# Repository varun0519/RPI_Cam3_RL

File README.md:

# RPI_Cam3_RL

## 🚀 How to Use Automation Script to generate fabrication outputs

### 🔧 Command Line (Terminal)

Run the following command **from the project directory** (where `.kicad_pro` file is located):

```bash
make
```
To generate zip of Gerbers for fabrication:
```bash
make release
```

Or run the script directly with Python:
```bash
python3 scripts/export_fab_outputs.py
```

### 3D view
#### Top View

#### Bottom View

#### Perspective View

### Schematic
[RPI_Cam3_RL_schematic.pdf](output/RPI_Cam3_RL_schematic.pdf)

### BOM
[RPI_Cam3_RL_BOM.xlsx](output/RPI_Cam3_RL_BOM.xlsx)

### Top Assembly
[RPI_Cam3_RL_Top_Assembly.pdf](output/RPI_Cam3_RL_Top_Assembly.pdf)

### Bottom Assembly
[RPI_Cam3_RL_Bottom_Assembly.pdf](output/RPI_Cam3_RL_Bottom_Assembly.pdf)

### Interactive BOM
Download and open [ibom.html](bom/ibom.html) in browser

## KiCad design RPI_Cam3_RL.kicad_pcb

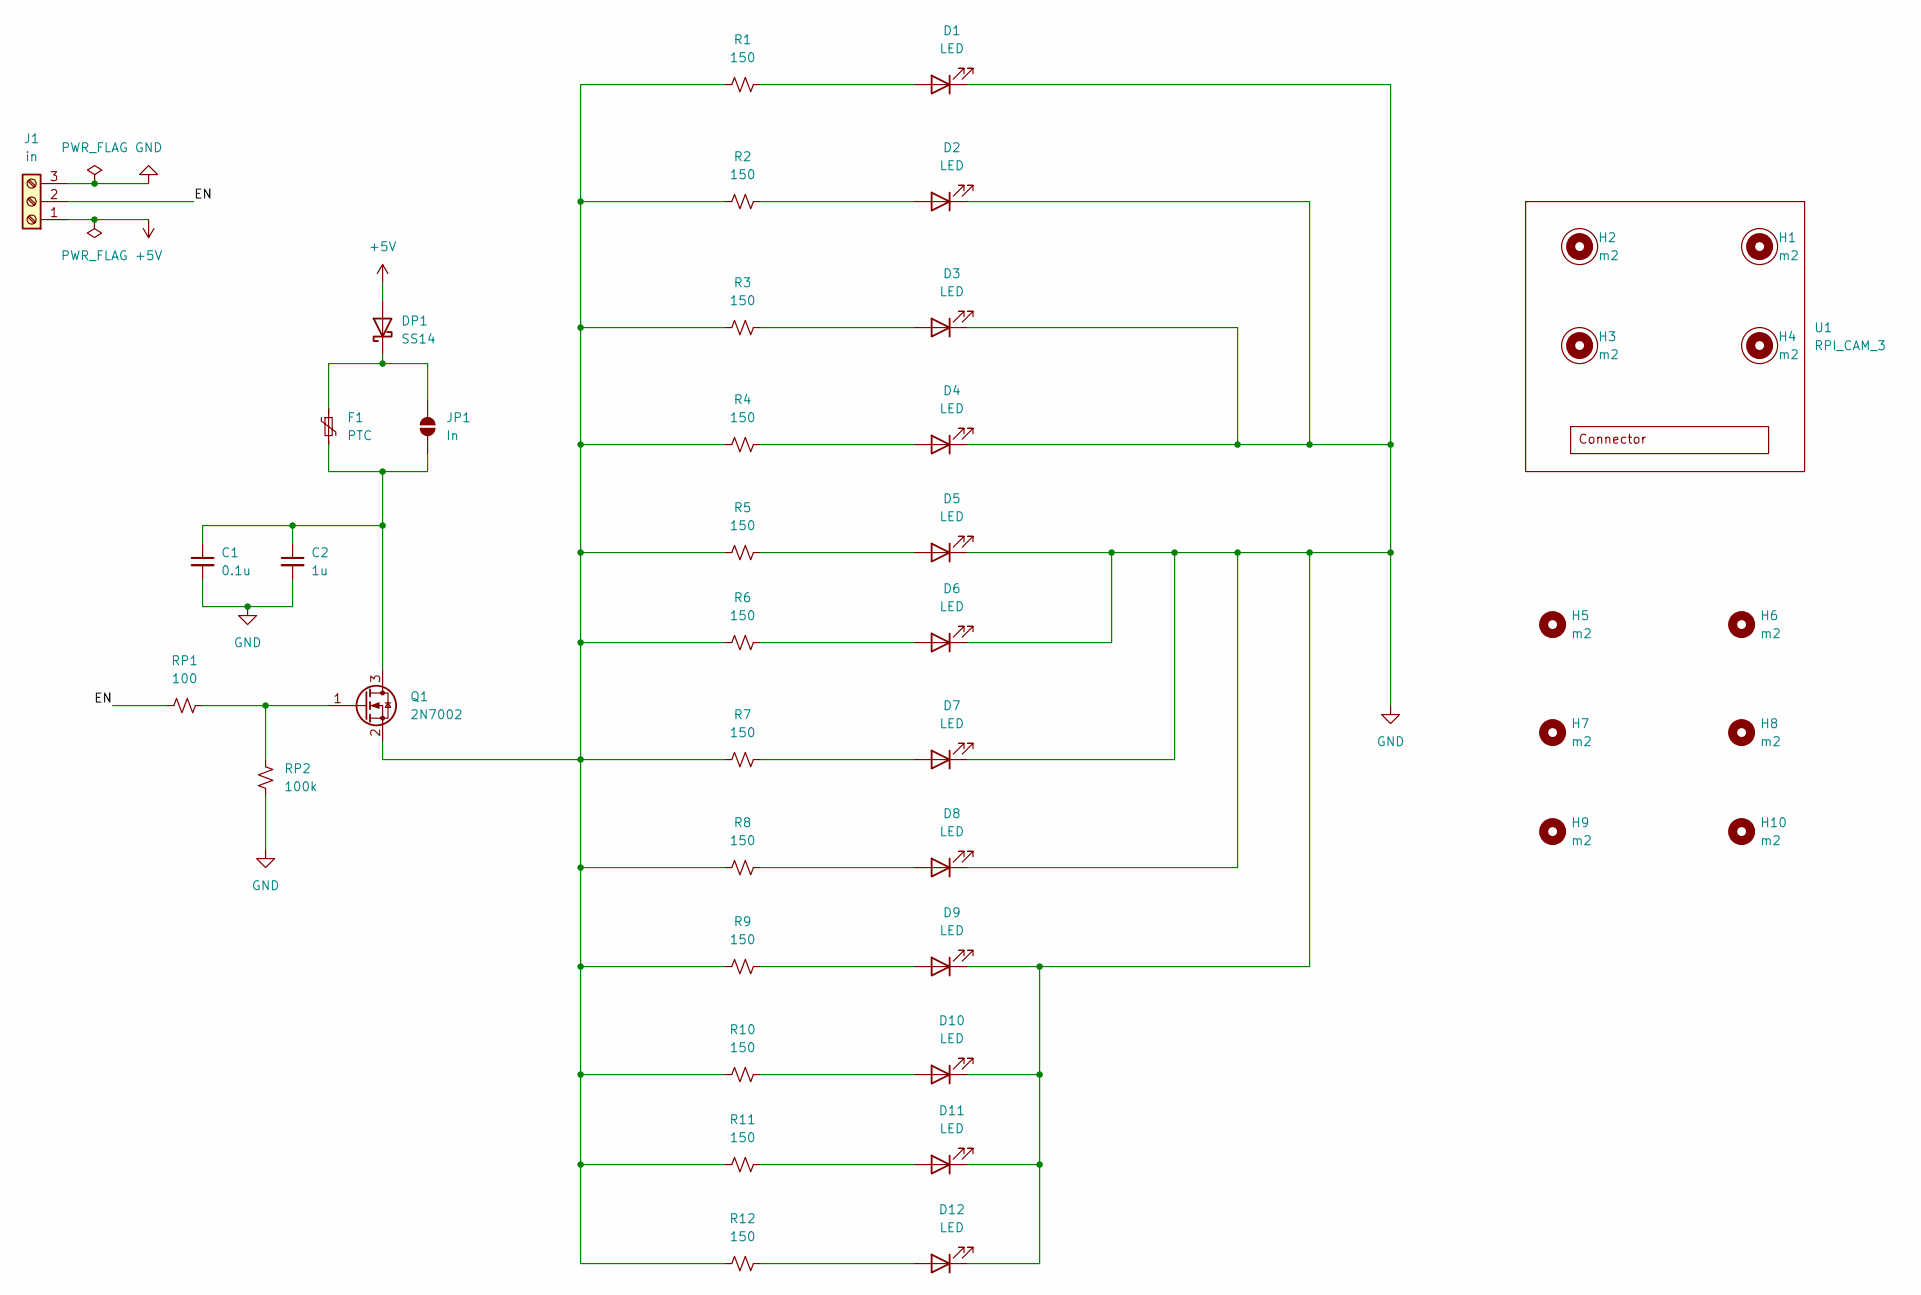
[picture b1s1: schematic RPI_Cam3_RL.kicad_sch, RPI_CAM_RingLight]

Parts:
C1: 0.1u; C_0805_2012Metric_Pad1.18x1.45mm_HandSolder
C2: 1u; C_0805_2012Metric_Pad1.18x1.45mm_HandSolder
D1, D2, D3, D4, D5, D6, D7, D8, D9, D10, D11, D12: LED; LED_PLCC_2835_Handsoldering
DP1: SS14; D_SMA
F1: PTC; R_0805_2012Metric_Pad1.20x1.40mm_HandSolder
H1, H2, H3, H4: m2; MountingHole_2.2mm_M2
H5, H6, H7, H8, H9, H10: m2; MountingHole_3.2mm_M3
J1: in; JST_EH_S3B-EH_1x03_P2.50mm_Horizontal
JP1: In; SolderJumper-2_P1.3mm_Open_RoundedPad1.0x1.5mm
Q1: 2N7002; SOT-23_Handsoldering
R1, R2, R3, R4, R5, R6, R7, R8, R9, R10, R11, R12: 150; R_0805_2012Metric_Pad1.20x1.40mm_HandSolder
RP1: 100; R_0805_2012Metric_Pad1.20x1.40mm_HandSolder
RP2: 100k; R_0805_2012Metric_Pad1.20x1.40mm_HandSolder
U1: RPI_CAM_3; RPI_Cam3

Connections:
+5V: DP1.2 (A), J1.1
/EN: J1.2, RP1.1
GND: C1.2, C2.2, D1.1 (K), D2.1 (K), D3.1 (K), D4.1 (K), D5.1 (K), D6.1 (K), D7.1 (K), D8.1 (K), D9.1 (K), D10.1 (K), D11.1 (K), D12.1 (K), J1.3, RP2.1
unnamed: D1.2 (A), R1.2
unnamed: D2.2 (A), R2.2
unnamed: D3.2 (A), R3.2
unnamed: D4.2 (A), R4.2
unnamed: D5.2 (A), R5.2
unnamed: D6.2 (A), R6.2
unnamed: D7.2 (A), R7.2
unnamed: D8.2 (A), R8.2
unnamed: D9.2 (A), R9.2
unnamed: D10.2 (A), R10.2
unnamed: D11.2 (A), R11.2
unnamed: D12.2 (A), R12.2
unnamed: DP1.1 (K), F1.1, JP1.2 (B)
unnamed: C1.1, C2.1, F1.2, JP1.1 (A), Q1.3 (D)
unnamed: Q1.1 (G), RP1.2, RP2.2
unnamed: Q1.2 (S), R1.1, R2.1, R3.1, R4.1, R5.1, R6.1, R7.1, R8.1, R9.1, R10.1, R11.1, R12.1

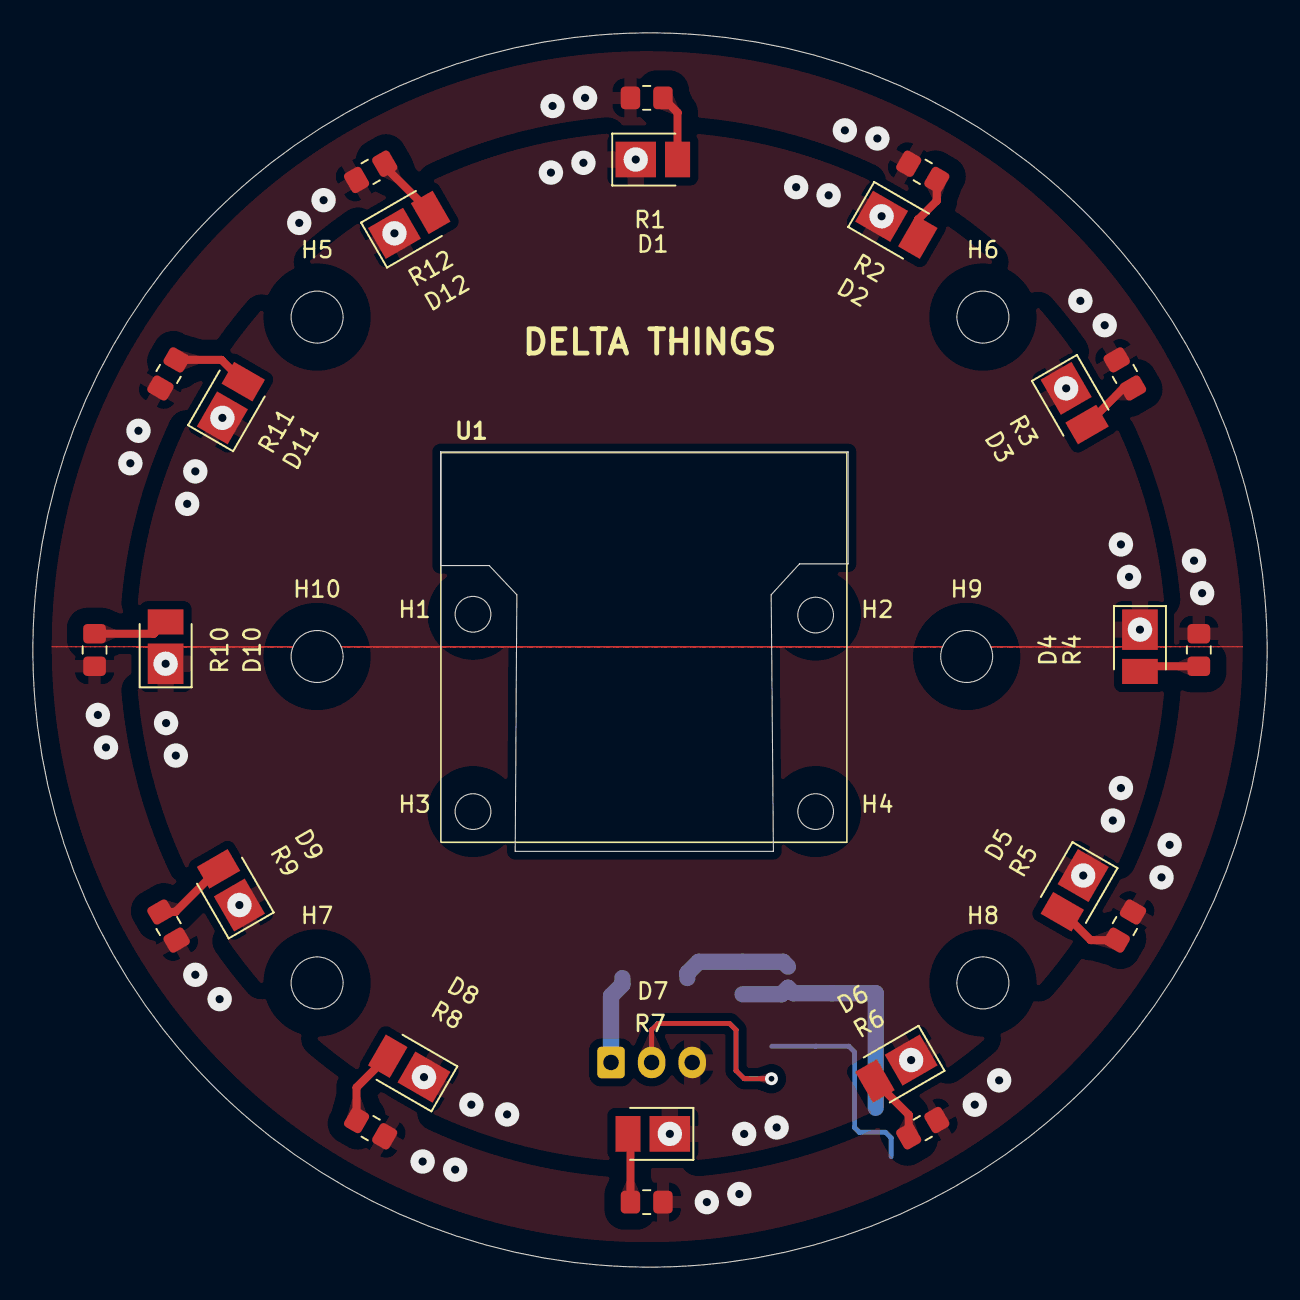
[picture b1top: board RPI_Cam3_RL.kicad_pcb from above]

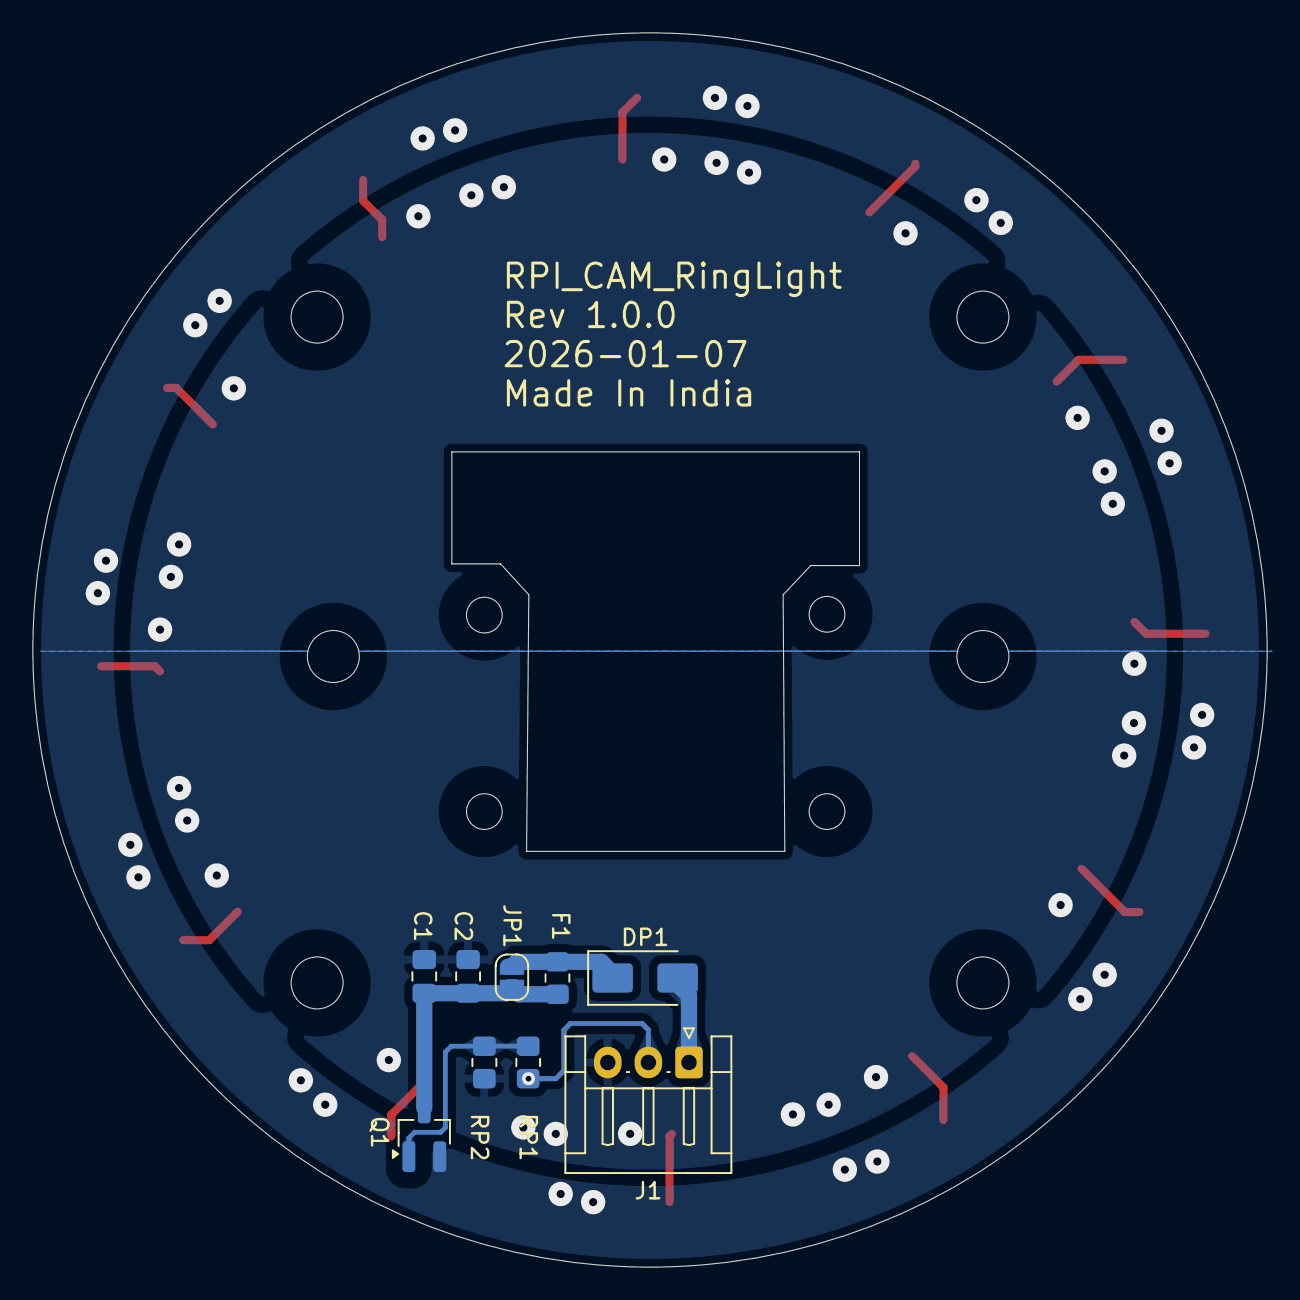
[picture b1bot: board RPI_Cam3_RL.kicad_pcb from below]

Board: 2 copper layers, 76.0 x 76.0 mm, 44 parts (9 on the bottom side), 19 nets.

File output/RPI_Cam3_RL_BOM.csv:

"ITEM_NUMBER","Reference","Value","Footprint","Description","QUANTITY","DNP","MPN","SKU","Link"
"1","C1","0.1u","Capacitor_SMD:C_0805_2012Metric_Pad1.18x1.45mm_HandSolder","Unpolarized capacitor, small symbol","1","","","",""
"2","C2","1u","Capacitor_SMD:C_0805_2012Metric_Pad1.18x1.45mm_HandSolder","Unpolarized capacitor, small symbol","1","","","",""
"3","D1,D2,D3,D4,D5,D6,D7,D8,D9,D10,D11,D12","LED","LED_SMD:LED_PLCC_2835_Handsoldering","Light emitting diode","12","","","",""
"4","DP1","SS14","Diode_SMD:D_SMA","40V 1A Schottky Diode, SMA","1","","","",""
"5","F1","PTC","Resistor_SMD:R_0805_2012Metric_Pad1.20x1.40mm_HandSolder","Resettable fuse, polymeric positive temperature coefficient, small symbol","1","","","",""
"6","J1","in","Connector_JST:JST_EH_S3B-EH_1x03_P2.50mm_Horizontal","Generic screw terminal, single row, 01x03, script generated (kicad-library-utils/schlib/autogen/connector/)","1","","","",""
"7","Q1","2N7002","Package_TO_SOT_SMD:SOT-23_Handsoldering","0.115A Id, 60V Vds, N-Channel MOSFET, SOT-23","1","","","",""
"8","R1,R2,R3,R4,R5,R6,R7,R8,R9,R10,R11,R12","150","Resistor_SMD:R_0805_2012Metric_Pad1.20x1.40mm_HandSolder","Resistor, small US symbol","12","","","",""
"9","RP1","100","Resistor_SMD:R_0805_2012Metric_Pad1.20x1.40mm_HandSolder","Resistor, small US symbol","1","","","",""
"10","RP2","100k","Resistor_SMD:R_0805_2012Metric_Pad1.20x1.40mm_HandSolder","Resistor, small US symbol","1","","","",""
"11","U1","RPI_CAM_3","RPICAM:RPI_Cam3","","1","","","",""

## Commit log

2025-12-25 First Draft
2025-12-25 Added Git Ignore
2025-12-29 MISC
2026-01-05 Updated Pcb Design -Small Radius
2026-01-06 Updated .gitignore
2026-01-07 Removed Ignore files
2026-01-07 Removed backup files
2026-01-07 design updates
2026-01-07 MakeFile
2026-01-07 silkscreen updates
